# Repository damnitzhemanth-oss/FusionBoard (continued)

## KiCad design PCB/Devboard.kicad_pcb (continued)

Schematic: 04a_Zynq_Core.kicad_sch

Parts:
C121, C122, C123, C124, C125, C126, C127, C128, C129, C130, C131, C132, C133, C134, C135, C136, C137, C138, C139, C140, C141, C142, C143, C144, C145, C146, C147, C148, C149, C150, C151, C152, C153, C155, C156, C157, C158, C159, C160, C161, C162, C163, C164, C165, C166, C167, C168, C169, C170, C171, C172, C173, C175, C176, C177, C178, C179, C180, C181, C182, C183, C184, C185, C186, C187, C188, C189, C190, C191, C192, C193, C194, C195, C196, C197, C198, C199, C200, C201, C202, C203, C204, C205, C206, C207, C208, C209, C210, C211, C212, C213, C214, C215, C216, C217, C218, C219, C220, C221, C222, C223, C224, C225, C226, C227, C228, C229, C230, C231, C232, C233, C234, C235, C236, C237, C238, C239, C240, C241, C242, C243, C244, C245, C246, C247, C248, C249, C250, C251: 0.1uF; C_0402_1005Metric
C154, C174: 47uF; C_1210_3225Metric
R103: 220Ω; R_0402_1005Metric
U27: xczu4evfbvb900pkg; XCZU4EVFBVB900PKG

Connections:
+0V9_GTR: C204.2, C206.2, C217.1, C219.1, U27.A10 (MGTAVCC_R), U27.C10 (MGTAVCC_R), U27.F8 (MGTAVCC_R), U27.H8 (MGTAVCC_R), U27.M8 (MGTAVCC_R), U27.P8 (MGTAVCC_R); also elsewhere on the board
+0V9_VCU: C166.2, C167.2, C183.1, C184.1, U27.AB18 (VCCINT_VCU), U27.AB19 (VCCINT_VCU), U27.AB20 (VCCINT_VCU), U27.AB21 (VCCINT_VCU), U27.V8 (VCCINT_IO); also elsewhere on the board
+0V85: C121.2, C135.2, C136.2, C137.2, C138.2, C139.2, C140.1, C154.1, C155.1, C156.1, C157.1, C158.1, U27.L11 (VCCINT), U27.L13 (VCCINT), U27.L17 (VCCINT), U27.M12 (VCCINT), U27.M14 (VCCINT), U27.M16 (VCCINT), U27.M18 (VCCINT), U27.N11 (VCCINT), U27.N13 (VCCINT), U27.N15 (VCCINT), U27.N17 (VCCINT), U27.P12 (VCCINT), U27.P14 (VCCINT), U27.P16 (VCCINT), U27.R10 (VCCBRAM), U27.R11 (VCCINT), U27.R13 (VCCINT), U27.R17 (VCCINT), U27.T9 (VCCINT_IO), U27.T10 (VCCBRAM), U27.T12 (VCCINT), U27.T16 (VCCINT), U27.U8 (VCCINT_IO), U27.U9 (VCCINT_IO), U27.U10 (VCCBRAM), U27.U11 (VCCINT), U27.U13 (VCCINT), U27.U17 (VCCINT), U27.V10 (VCCBRAM), U27.V12 (VCCINT), U27.V16 (VCCINT), U27.W11 (VCCINT), U27.W13 (VCCINT), U27.W15 (VCCINT), U27.Y12 (VCCINT), U27.Y14 (VCCINT); also elsewhere on the board
+0V85_GTR: C192.2, C201.1, U27.J23 (PS_MGTRAVCC), U27.L23 (PS_MGTRAVCC); also elsewhere on the board
+0V85_PS: C159.2, C161.2, C162.2, C164.2, C165.2, C172.2, C173.2, C174.1, C176.1, C178.1, C179.1, C181.1, C182.1, U27.AA18 (VCC_PSINTFP), U27.AA20 (VCC_PSINTFP), U27.AA21 (VCC_PSINTFP_DDR), U27.AA22 (VCC_PSINTFP_DDR), U27.V17 (VCC_PSINTLP), U27.V18 (VCC_PSINTLP), U27.V19 (VCC_PSINTLP), U27.W17 (VCC_PSINTLP), U27.W19 (VCC_PSINTLP), U27.W20 (VCC_PSINTLP), U27.Y16 (VCC_PSINTFP), U27.Y17 (VCC_PSINTFP), U27.Y18 (VCC_PSINTFP), U27.Y19 (VCC_PSINTFP), U27.Y20 (VCC_PSINTFP), U27.Y22 (VCC_PSINTFP_DDR); also elsewhere on the board
+1V2: C189.2, C191.2, C195.2, C198.1, C200.1, U27.AA4 (VCCO_66), U27.AA24 (VCCO_PSDDR_504), U27.AB27 (VCCO_PSDDR_504), U27.AC25 (VCCO_PSDDR_504), U27.AD3 (VCCO_66), U27.AD8 (VCCO_66), U27.AD28 (VCCO_PSDDR_504), U27.AE26 (VCCO_PSDDR_504), U27.AG27 (VCCO_PSDDR_504), U27.AK26 (VCCO_PSDDR_504); also elsewhere on the board
+1V2_GTH: C207.2, C211.2, C214.2, C215.1, C220.1, C224.1, U27.A6 (MGTAVTT_R), U27.B8 (MGTAVTT_R), U27.C6 (MGTAVTT_R), U27.D8 (MGTAVTT_R), U27.E6 (MGTAVTT_R), U27.G6 (MGTAVTT_R), U27.J6 (MGTAVTT_R), U27.L6 (MGTAVTT_R), U27.N6 (MGTAVTT_R), U27.R6 (MGTAVTT_R), U27.U6 (MGTAVTT_R); also elsewhere on the board
+1V2_PS: C194.2, C203.1, U27.U18 (VCC_PSDDR_PLL), U27.U19 (VCC_PSDDR_PLL); also elsewhere on the board
+1V8: C168.2, C169.2, C170.2, C171.2, C175.2, C185.1, C186.1, C187.1, C188.1, C212.2, C225.1, C229.2, C230.2, C231.2, C232.2, C238.2, C239.1, C243.1, C244.1, C245.1, C246.1, U27.AC15 (VCCO_64), U27.AE11 (VCCO_65), U27.AF14 (VCCO_64), U27.AG7 (VCCO_65), U27.AG17 (VCCO_64), U27.AH10 (VCCO_65), U27.E10 (MGTVCCAUX_R), U27.G10 (MGTVCCAUX_R), U27.K10 (VCCAUX), U27.L10 (VCCAUX), U27.M10 (VCCAUX_IO), U27.N10 (VCCAUX_IO), U27.P10 (VCCAUX_IO), U27.R15 (VCCADC), U27.T22 (VCC_PSAUX), U27.U21 (VCC_PSAUX), U27.V21 (VCC_PSAUX), U27.V22 (VCC_PSAUX); also elsewhere on the board
+1V8_CLEAN: C193.2, C196.2, C202.1, U27.T18 (VCC_PSPLL), U27.T20 (VCC_PSPLL), U27.T21 (VCC_PSPLL); also elsewhere on the board
+1V8_MGTRAVTT: C213.2, C216.2, C226.1, U27.H25 (PS_MGTRAVTT), U27.K25 (PS_MGTRAVTT), U27.L27 (PS_MGTRAVTT); also elsewhere on the board
+1V8_VCCADC: C197.2, U27.W22 (VCC_PSADC); also elsewhere on the board
+3V3: C227.2, C228.2, C233.2, C237.2, C240.2, C241.1, C242.1, C247.1, C251.1, U27.B22 (VCCO_PSIO1_501), U27.B27 (VCCO_PSIO2_502), U27.D13 (VCCO_46), U27.D18 (VCCO_PSIO0_500), U27.D23 (VCCO_PSIO1_501), U27.D28 (VCCO_PSIO2_502), U27.E16 (VCCO_45), U27.E21 (VCCO_PSIO1_501), U27.E26 (VCCO_PSIO2_502), U27.F19 (VCCO_PSIO0_500), U27.G12 (VCCO_46), U27.H15 (VCCO_45), U27.J18 (VCCO_PSIO0_500), U27.N20 (VCCO_PSIO3_503), U27.P18 (VCCO_PSIO3_503); also elsewhere on the board
ADC_CLKOUTM: U27.AE9 (IO_L10P_T1U_N6_QBC_AD4P_65); also elsewhere on the board
ADC_CLKOUTP: U27.AE8 (IO_L10N_T1U_N7_QBC_AD4N_65); also elsewhere on the board
ADC_DA0_M: U27.AK10 (IO_L5N_T0U_N9_AD14N_65); also elsewhere on the board
ADC_DA0_P: U27.AJ10 (IO_L5P_T0U_N8_AD14P_65); also elsewhere on the board
ADC_DA2_M: U27.AJ9 (IO_L8N_T1L_N3_AD5N_65); also elsewhere on the board
ADC_DA2_P: U27.AH9 (IO_L8P_T1L_N2_AD5P_65); also elsewhere on the board
ADC_DA4_M: U27.AK11 (IO_L4N_T0U_N7_DBC_AD7N_65); also elsewhere on the board
ADC_DA4_P: U27.AJ11 (IO_L4P_T0U_N6_DBC_AD7P_SMBALERT_65); also elsewhere on the board
ADC_DA6_M: U27.AJ7 (IO_L12N_T1U_N11_GC_65); also elsewhere on the board
ADC_DA6_P: U27.AJ6 (IO_L13N_T2L_N1_GC_QBC_65); also elsewhere on the board
ADC_DA8_M: U27.AH7 (IO_L12P_T1U_N10_GC_65); also elsewhere on the board
ADC_DA8_P: U27.AH8 (IO_L11N_T1U_N9_GC_65); also elsewhere on the board
ADC_DA10_M: U27.AG10 (IO_L6N_T0U_N11_AD6N_65); also elsewhere on the board
ADC_DA10_P: U27.AF10 (IO_L6P_T0U_N10_AD6P_65); also elsewhere on the board
ADC_DA12_M: U27.AF7 (IO_L9N_T1L_N5_AD12N_65); also elsewhere on the board
ADC_DA12_P: U27.AF8 (IO_L9P_T1L_N4_AD12P_65); also elsewhere on the board
ADC_DB0_M: U27.AK7 (IO_L15P_T2L_N4_AD11P_65); also elsewhere on the board
ADC_DB0_P: U27.AK6 (IO_L15N_T2L_N5_AD11N_65); also elsewhere on the board
ADC_DB2_M: U27.AJ4 (IO_L17P_T2U_N8_AD10P_65); also elsewhere on the board
ADC_DB2_P: U27.AK4 (IO_L17N_T2U_N9_AD10N_65); also elsewhere on the board
ADC_DB4_M: U27.AF5 (IO_L18N_T2U_N11_AD2N_65); also elsewhere on the board
ADC_DB4_P: U27.AF6 (IO_L18P_T2U_N10_AD2P_65); also elsewhere on the board
ADC_DB6_M: U27.AJ1 (IO_L20N_T3L_N3_AD1N_65); also elsewhere on the board
ADC_DB6_P: U27.AJ2 (IO_L20P_T3L_N2_AD1P_65); also elsewhere on the board
ADC_DB8_M: U27.AK2 (IO_L19N_T3L_N1_DBC_AD9N_65); also elsewhere on the board
ADC_DB8_P: U27.AK3 (IO_L19P_T3L_N0_DBC_AD9P_65); also elsewhere on the board
ADC_DB10_M: U27.AG3 (IO_L22N_T3U_N7_DBC_AD0N_65); also elsewhere on the board
ADC_DB10_P: U27.AG4 (IO_L22P_T3U_N6_DBC_AD0P_65); also elsewhere on the board
ADC_DB12_M: U27.AH2 (IO_L21N_T3L_N5_AD8N_65); also elsewhere on the board
ADC_DB12_P: U27.AH3 (IO_L21P_T3L_N4_AD8P_65); also elsewhere on the board
ADS_CS: U27.G16 (IO_L5P_HDGC_45); also elsewhere on the board
ADS_DIN: U27.E17 (IO_L7P_HDGC_45); also elsewhere on the board
ADS_DOUT: U27.E15 (IO_L8P_HDGC_45); also elsewhere on the board
ADS_DRDY: U27.D16 (IO_L9P_AD11P_45); also elsewhere on the board
ADS_SCLK: U27.F16 (IO_L6P_HDGC_45); also elsewhere on the board
ADS_SYNC: U27.C17 (IO_L10P_AD10P_45); also elsewhere on the board
CAM_PWDN: U27.F18 (PS_MIO10); also elsewhere on the board
CAM_RST_N: U27.H18 (PS_MIO12); also elsewhere on the board
DP_AUX_N: U27.E20 (PS_MIO8); also elsewhere on the board
DP_AUX_P: U27.E19 (PS_MIO7); also elsewhere on the board
DP_RX0_N: U27.H28 (PS_MGTRRXN2_505)
DP_RX0_P: U27.H27 (PS_MGTRRXP2_505)
DP_TX0_N: U27.J26 (PS_MGTRTXN2_505); also elsewhere on the board
DP_TX0_P: U27.J25 (PS_MGTRTXP2_505); also elsewhere on the board
EXP_LANE0_RX_N: U27.C3 (MGTHRXN1_226)
EXP_LANE0_RX_P: U27.C4 (MGTHRXP1_226)
EXP_LANE0_TX_N: U27.C7 (MGTHTXN1_226)
EXP_LANE0_TX_P: U27.C8 (MGTHTXP1_226)
EXP_LANE1_RX_N: U27.B1 (MGTHRXN2_226)
EXP_LANE1_RX_P: U27.B2 (MGTHRXP2_226)
EXP_LANE1_TX_N: U27.B5 (MGTHTXN2_226)
EXP_LANE1_TX_P: U27.B6 (MGTHTXP2_226)
EXP_LANE2_RX_N: U27.A3 (MGTHRXN3_226)
EXP_LANE2_RX_P: U27.A4 (MGTHRXP3_226)
EXP_LANE2_TX_N: U27.A7 (MGTHTXN3_226)
EXP_LANE2_TX_P: U27.A8 (MGTHTXP3_226)
EXP_LANE3_RX_N: U27.H1 (MGTHRXN0_225)
EXP_LANE3_RX_P: U27.H2 (MGTHRXP0_225)
EXP_LANE3_TX_N: U27.H5 (MGTHTXN0_225)
EXP_LANE3_TX_P: U27.H6 (MGTHTXP0_225)
EXP_LANE4_RX_N: U27.G3 (MGTHRXN1_225)
EXP_LANE4_RX_P: U27.G4 (MGTHRXP1_225)
EXP_LANE4_TX_N: U27.G7 (MGTHTXN1_225)
EXP_LANE4_TX_P: U27.G8 (MGTHTXP1_225)
FAN_TACH: U27.J21 (PS_MIO48); also elsewhere on the board
GEM_RST: U27.C23 (PS_MIO38); also elsewhere on the board
GEM_RXC: U27.D26 (PS_MIO70); also elsewhere on the board
GEM_RXD0: U27.D30 (PS_MIO71); also elsewhere on the board
GEM_RXD1: U27.E27 (PS_MIO72); also elsewhere on the board
GEM_RXD2: U27.E30 (PS_MIO73); also elsewhere on the board
GEM_RXD3: U27.E29 (PS_MIO74); also elsewhere on the board
GEM_RX_CTL: U27.D29 (PS_MIO75); also elsewhere on the board
GEM_TXC: U27.B30 (PS_MIO64); also elsewhere on the board
GEM_TXD0: U27.D25 (PS_MIO65); also elsewhere on the board
GEM_TXD1: U27.C27 (PS_MIO66); also elsewhere on the board
GEM_TXD2: U27.C28 (PS_MIO67); also elsewhere on the board
GEM_TXD3: U27.C29 (PS_MIO68); also elsewhere on the board
GEM_TX_CTL: U27.D27 (PS_MIO69); also elsewhere on the board
GND: C121.1, C122.1, C123.1, C124.1, C125.1, C126.1, C127.1, C128.1, C129.1, C130.1, C131.1, C132.1, C133.1, C134.1, C135.1, C136.1, C137.1, C138.1, C139.1, C140.2, C141.2, C142.2, C143.2, C144.2, C145.2, C146.2, C147.2, C148.2, C149.2, C150.2, C151.2, C152.2, C153.2, C154.2, C155.2, C156.2, C157.2, C158.2, C159.1, C160.1, C161.1, C162.1, C163.1, C164.1, C165.1, C166.1, C167.1, C168.1, C169.1, C170.1, C171.1, C172.1, C173.1, C174.2, C175.1, C176.2, C177.2, C178.2, C179.2, C180.2, C181.2, C182.2, C183.2, C184.2, C185.2, C186.2, C187.2, C188.2, C189.1, C190.1, C191.1, C193.1, C194.1, C195.1, C196.1, C197.1, C198.2, C199.2, C200.2, C202.2, C203.2, C204.1, C205.1, C206.1, C207.1, C208.1, C209.1, C210.1, C211.1, C212.1, C213.1, C214.1, C215.2, C216.1, C217.2, C218.2, C219.2, C220.2, C221.2, C222.2, C223.2, C224.2, C225.2, C226.2, C227.1, C228.1, C229.1, C230.1, C231.1, C232.1, C233.1, C234.1, C235.1, C236.1, C237.1, C238.1, C239.2, C240.1, C241.2, C242.2, C243.2, C244.2, C245.2, C246.2, C247.2, C248.2, C249.2, C250.2, C251.2, R103.2, U27.A1 (GND), U27.A2 (GND), U27.A5 (GND), U27.A9 (GND), U27.A11 (GND), U27.A30 (GND), U27.AA9 (GND), U27.AA19 (GND), U27.AA29 (GND), U27.AB2 (GND), U27.AB7 (GND), U27.AB12 (GND), U27.AB17 (GND), U27.AB22 (GND), U27.AC5 (GND), U27.AC10 (GND), U27.AC20 (GND), U27.AD13 (GND), U27.AD18 (GND), U27.AD23 (GND), U27.AE6 (GND), U27.AE16 (GND), U27.AE21 (GND), U27.AF4 (GND), U27.AF9 (GND), U27.AF19 (GND), U27.AF24 (GND), U27.AF29 (GND), U27.AG2 (GND), U27.AG12 (GND), U27.AG22 (GND), U27.AH5 (GND), U27.AH15 (GND), U27.AH20 (GND), U27.AH25 (GND), U27.AJ3 (GND), U27.AJ8 (GND), U27.AJ13 (GND), U27.AJ18 (GND), U27.AJ23 (GND), U27.AJ28 (GND), U27.AK1 (GND), U27.AK30 (GND), U27.B3 (GND), U27.B4 (GND), U27.B7 (GND), U27.B11 (GND), U27.B13 (GND), U27.B17 (GND), U27.C1 (GND), U27.C2 (GND), U27.C5 (GND), U27.C9 (GND), U27.C11 (GND), U27.C15 (GND), U27.C20 (GND), U27.C25 (GND), U27.C30 (GND), U27.D3 (GND), U27.D4 (GND), U27.D7 (GND), U27.D11 (GND), U27.E1 (GND), U27.E2 (GND), U27.E5 (GND), U27.E9 (GND), U27.E11 (GND), U27.F3 (GND), U27.F4 (GND), U27.F7 (GND), U27.F11 (GND), U27.F14 (GND), U27.F24 (GND), U27.F25 (GND), U27.F26 (GND), U27.F27 (GND), U27.F28 (GND), U27.F29 (GND), U27.F30 (GND), U27.G1 (GND), U27.G2 (GND), U27.G5 (GND), U27.G9 (GND), U27.G11 (GND), U27.G17 (GND), U27.G22 (GND), U27.G23 (GND), U27.G24 (GND), U27.G27 (GND), U27.G28 (GND), U27.H3 (GND), U27.H4 (GND), U27.H7 (GND), U27.H11 (GND), U27.H20 (GND), U27.H22 (GND), U27.H26 (GND), U27.H29 (GND), U27.H30 (GND), U27.J1 (GND), U27.J2 (GND), U27.J5 (GND), U27.J9 (GND), U27.J10 (GND), U27.J11 (GND), U27.J13 (GND), U27.J22 (GND), U27.J24 (GND), U27.J27 (GND), U27.J28 (GND), U27.K3 (GND), U27.K4 (GND), U27.K9 (GND), U27.K22 (GND), U27.K26 (GND), U27.K29 (GND), U27.K30 (GND), U27.L1 (GND), U27.L2 (GND), U27.L5 (GND), U27.L9 (GND), U27.L12 (GND), U27.L16 (GND), U27.L18 (GND), U27.L22 (GND), U27.L24 (GND), U27.L28 (GND), U27.M3 (GND), U27.M4 (GND), U27.M7 (GND), U27.M9 (GND), U27.M11 (GND), U27.M13 (GND), U27.M15 (GND), U27.M17 (GND), U27.M22 (GND), U27.M26 (GND), U27.M29 (GND), U27.M30 (GND), U27.N1 (GND), U27.N2 (GND), U27.N5 (GND), U27.N9 (GND), U27.N12 (GND), U27.N14 (GND), U27.N16 (GND), U27.N23 (GND), U27.N24 (GND), U27.N25 (GND), U27.N26 (GND), U27.N27 (GND), U27.N28 (GND), U27.N29 (GND), U27.N30 (GND), U27.P3 (GND), U27.P4 (GND), U27.P7 (GND), U27.P9 (GND), U27.P11 (GND), U27.P13 (GND), U27.P15 (GND), U27.P17 (GND), U27.R1 (GND), U27.R2 (GND), U27.R5 (GND), U27.R9 (GND), U27.R12 (GND), U27.R14 (GNDADC), U27.R16 (GND), U27.R21 (GND), U27.R26 (GND), U27.T3 (GND), U27.T4 (GND), U27.T7 (GND), U27.T8 (GND), U27.T11 (GND), U27.T13 (GND), U27.T14 (VREFN), U27.T17 (GND), U27.T19 (GND), U27.T24 (GND), U27.T29 (GND), U27.U1 (GND), U27.U2 (GND), U27.U5 (GND), U27.U7 (GND), U27.U12 (GND), U27.U16 (GND), U27.U20 (VCC_PSBATT), U27.U22 (GND), U27.U27 (GND), U27.V3 (GND), U27.V4 (GND), U27.V7 (GND), U27.V9 (GND), U27.V11 (GND), U27.V13 (GND), U27.V20 (GND), U27.V25 (GND), U27.W1 (GND), U27.W2 (GND), U27.W5 (GND), U27.W6 (GND), U27.W12 (GND), U27.W14 (GND), U27.W16 (GND), U27.W18 (GND), U27.W21 (GND_PSADC), U27.W23 (GND), U27.W28 (GND), U27.Y2 (GND), U27.Y3 (GND), U27.Y4 (GND), U27.Y5 (GND), U27.Y11 (GND), U27.Y13 (GND), U27.Y15 (GND), U27.Y21 (GND), U27.Y26 (GND); also elsewhere on the board
GNSS_PPS: U27.F20 (PS_MIO9); also elsewhere on the board
GPIO_BMC_IRQ: U27.B24 (PS_MIO34)
GPIO_BOOT_LED: U27.F21 (PS_MIO37)
GPIO_ESP_IRQ: U27.K21 (PS_MIO47)
GPIO_EXP_RST: U27.K20 (PS_MIO46)
GPIO_PD_IRQ: U27.B23 (PS_MIO35), U27.G18 (PS_MIO11)
GPIO_SD1_PWR_EN: U27.D22 (PS_MIO36)
GTH_REFCLK0_156M_N: U27.D9 (MGTREFCLK0N_226)
GTH_REFCLK0_156M_P: U27.D10 (MGTREFCLK0P_226)
GTH_REFCLK1_156M_N: U27.B9 (MGTREFCLK1N_226)
GTH_REFCLK1_156M_P: U27.B10 (MGTREFCLK1P_226)
I2C0_SCL: U27.A22 (PS_MIO31); also elsewhere on the board
I2C0_SDA: U27.C22 (PS_MIO33); also elsewhere on the board
I2C1_SCL: U27.C21 (PS_MIO30); also elsewhere on the board
I2C1_SDA: U27.G20 (PS_MIO32); also elsewhere on the board
LMS_SCK: U27.J16 (IO_L4P_AD12P_45); also elsewhere on the board
LMX_CSB: U27.J15 (IO_L3P_AD13P_45); also elsewhere on the board
LMX_MUXOUT: U27.L15 (IO_L1P_AD15P_45); also elsewhere on the board
LMX_SDI: U27.K15 (IO_L2P_AD14P_45); also elsewhere on the board
MDIO_MDC: U27.E28 (PS_MIO76); also elsewhere on the board
MDIO_MDIO: U27.E25 (PS_MIO77); also elsewhere on the board
MIO50: U27.J20 (PS_MIO50); also elsewhere on the board
MIO51: U27.H21 (PS_MIO51); also elsewhere on the board
MIPI_CLK_N: U27.AC11 (IO_L3N_T0L_N5_AD15N_66); also elsewhere on the board
MIPI_CLK_P: U27.AB11 (IO_L3P_T0L_N4_AD15P_66); also elsewhere on the board
MIPI_D0_N: U27.AA11 (IO_L2N_T0L_N3_66); also elsewhere on the board
MIPI_D0_P: U27.AA12 (IO_L2P_T0L_N2_66); also elsewhere on the board
MIPI_D1_N: U27.AD12 (IO_L1N_T0L_N1_DBC_66); also elsewhere on the board
MIPI_D1_P: U27.AC12 (IO_L1P_T0L_N0_DBC_66); also elsewhere on the board
MIPI_D2_N: U27.AD10 (IO_L4N_T0U_N7_DBC_AD7N_66); also elsewhere on the board
MIPI_D2_P: U27.AD11 (IO_L4P_T0U_N6_DBC_AD7P_66); also elsewhere on the board
MIPI_D3_N: U27.AB9 (IO_L5N_T0U_N9_AD14N_66); also elsewhere on the board
MIPI_D3_P: U27.AB10 (IO_L5P_T0U_N8_AD14P_66); also elsewhere on the board
unnamed: C122.2, C141.1
unnamed: C123.2, C142.1
unnamed: C124.2, C143.1
unnamed: C125.2, C144.1
unnamed: C126.2, C145.1
unnamed: C127.2, C146.1
unnamed: C128.2, C147.1
unnamed: C129.2, C148.1
unnamed: C130.2, C149.1
unnamed: C131.2, C150.1
unnamed: C132.2, C151.1
unnamed: C133.2, C152.1
unnamed: C134.2, C153.1
unnamed: C160.2, C177.1
unnamed: C163.2, C180.1
unnamed: C190.2, C199.1
unnamed: C192.1, C201.2
unnamed: C205.2, C218.1
unnamed: C208.2, C221.1
unnamed: C209.2, C222.1
unnamed: C210.2, C223.1
unnamed: C234.2, C248.1
unnamed: C235.2, C249.1
unnamed: C236.2, C250.1
unnamed: R103.1, U27.M25 (PS_MGTRREF_505)
PCIE_RX_N: U27.J30 (PS_MGTRRXN1_505); also elsewhere on the board
PCIE_RX_P: U27.J29 (PS_MGTRRXP1_505); also elsewhere on the board
PCIE_TX_N: U27.K28 (PS_MGTRTXN1_505); also elsewhere on the board
PCIE_TX_P: U27.K27 (PS_MGTRTXP1_505); also elsewhere on the board
PS_DDR_A0: U27.AH30 (PS_DDR_A0); also elsewhere on the board
PS_DDR_A1: U27.AG30 (PS_DDR_A1); also elsewhere on the board
PS_DDR_A2: U27.AK29 (PS_DDR_A2); also elsewhere on the board
PS_DDR_A3: U27.AJ30 (PS_DDR_A3); also elsewhere on the board
PS_DDR_A4: U27.AK28 (PS_DDR_A4); also elsewhere on the board
PS_DDR_A5: U27.AK27 (PS_DDR_A5); also elsewhere on the board
PS_DDR_A6: U27.AF27 (PS_DDR_A6); also elsewhere on the board
PS_DDR_A7: U27.AE27 (PS_DDR_A7); also elsewhere on the board
PS_DDR_A8: U27.AF26 (PS_DDR_A8); also elsewhere on the board
PS_DDR_A9: U27.AG26 (PS_DDR_A9); also elsewhere on the board
PS_DDR_A10: U27.AE29 (PS_DDR_A10); also elsewhere on the board
PS_DDR_A11: U27.AE28 (PS_DDR_A11); also elsewhere on the board
PS_DDR_A12: U27.AH29 (PS_DDR_A12); also elsewhere on the board
PS_DDR_A13: U27.AH28 (PS_DDR_A13); also elsewhere on the board
PS_DDR_A14: U27.AG29 (PS_DDR_A14); also elsewhere on the board
PS_DDR_A15: U27.AJ29 (PS_DDR_A15); also elsewhere on the board
PS_DDR_A16: U27.AH27 (PS_DDR_A16); also elsewhere on the board
PS_DDR_A17: U27.AJ27 (PS_DDR_A17)
PS_DDR_ACT_N: U27.AD26 (PS_DDR_ACT_N); also elsewhere on the board
PS_DDR_ALERT_N: U27.AB24 (PS_DDR_ALERT_N); also elsewhere on the board
PS_DDR_BA0: U27.AD27 (PS_DDR_BA0); also elsewhere on the board
PS_DDR_BA1: U27.AC26 (PS_DDR_BA1); also elsewhere on the board
PS_DDR_BG0: U27.AC28 (PS_DDR_BG0); also elsewhere on the board
PS_DDR_BG1: U27.AC27 (PS_DDR_BG1)
PS_DDR_CK0: U27.AE30 (PS_DDR_CK0); also elsewhere on the board
PS_DDR_CK1: U27.AF28 (PS_DDR_CK1)
PS_DDR_CKE0: U27.AC30 (PS_DDR_CKE0); also elsewhere on the board
PS_DDR_CKE1: U27.AB28 (PS_DDR_CKE1)
PS_DDR_CK_N0: U27.AF30 (PS_DDR_CK_N0); also elsewhere on the board
PS_DDR_CK_N1: U27.AG28 (PS_DDR_CK_N1)
PS_DDR_CS_N0: U27.AD30 (PS_DDR_CS_N0); also elsewhere on the board
PS_DDR_CS_N1: U27.AD29 (PS_DDR_CS_N1)
PS_DDR_DM0: U27.AJ20 (PS_DDR_DM0); also elsewhere on the board
PS_DDR_DM1: U27.AJ25 (PS_DDR_DM1); also elsewhere on the board
PS_DDR_DM2: U27.AF21 (PS_DDR_DM2); also elsewhere on the board
PS_DDR_DM3: U27.AE25 (PS_DDR_DM3); also elsewhere on the board
PS_DDR_DM4: U27.Y24 (PS_DDR_DM4); also elsewhere on the board
PS_DDR_DM5: U27.R24 (PS_DDR_DM5); also elsewhere on the board
PS_DDR_DM6: U27.V28 (PS_DDR_DM6); also elsewhere on the board
PS_DDR_DM7: U27.P28 (PS_DDR_DM7); also elsewhere on the board
PS_DDR_DM8: U27.AA27 (PS_DDR_DM8)
PS_DDR_DQ0: U27.AH22 (PS_DDR_DQ0); also elsewhere on the board
PS_DDR_DQ1: U27.AH21 (PS_DDR_DQ1); also elsewhere on the board
PS_DDR_DQ2: U27.AJ22 (PS_DDR_DQ2); also elsewhere on the board
PS_DDR_DQ3: U27.AK22 (PS_DDR_DQ3); also elsewhere on the board
PS_DDR_DQ4: U27.AK20 (PS_DDR_DQ4); also elsewhere on the board
PS_DDR_DQ5: U27.AJ19 (PS_DDR_DQ5); also elsewhere on the board
PS_DDR_DQ6: U27.AK19 (PS_DDR_DQ6); also elsewhere on the board
PS_DDR_DQ7: U27.AH19 (PS_DDR_DQ7); also elsewhere on the board
PS_DDR_DQ8: U27.AH23 (PS_DDR_DQ8); also elsewhere on the board
PS_DDR_DQ9: U27.AK23 (PS_DDR_DQ9); also elsewhere on the board
PS_DDR_DQ10: U27.AG24 (PS_DDR_DQ10); also elsewhere on the board
PS_DDR_DQ11: U27.AK24 (PS_DDR_DQ11); also elsewhere on the board
PS_DDR_DQ12: U27.AJ26 (PS_DDR_DQ12); also elsewhere on the board
PS_DDR_DQ13: U27.AK25 (PS_DDR_DQ13); also elsewhere on the board
PS_DDR_DQ14: U27.AG25 (PS_DDR_DQ14); also elsewhere on the board
PS_DDR_DQ15: U27.AH26 (PS_DDR_DQ15); also elsewhere on the board
PS_DDR_DQ16: U27.AD22 (PS_DDR_DQ16); also elsewhere on the board
PS_DDR_DQ17: U27.AE22 (PS_DDR_DQ17); also elsewhere on the board
PS_DDR_DQ18: U27.AF22 (PS_DDR_DQ18); also elsewhere on the board
PS_DDR_DQ19: U27.AG21 (PS_DDR_DQ19); also elsewhere on the board
PS_DDR_DQ20: U27.AD20 (PS_DDR_DQ20); also elsewhere on the board
PS_DDR_DQ21: U27.AF20 (PS_DDR_DQ21); also elsewhere on the board
PS_DDR_DQ22: U27.AE20 (PS_DDR_DQ22); also elsewhere on the board
PS_DDR_DQ23: U27.AG20 (PS_DDR_DQ23); also elsewhere on the board
PS_DDR_DQ24: U27.AG23 (PS_DDR_DQ24); also elsewhere on the board
PS_DDR_DQ25: U27.AF23 (PS_DDR_DQ25); also elsewhere on the board
PS_DDR_DQ26: U27.AF25 (PS_DDR_DQ26); also elsewhere on the board
PS_DDR_DQ27: U27.AE23 (PS_DDR_DQ27); also elsewhere on the board
PS_DDR_DQ28: U27.AC22 (PS_DDR_DQ28); also elsewhere on the board
PS_DDR_DQ29: U27.AC23 (PS_DDR_DQ29); also elsewhere on the board
PS_DDR_DQ30: U27.AD25 (PS_DDR_DQ30); also elsewhere on the board
PS_DDR_DQ31: U27.AC24 (PS_DDR_DQ31); also elsewhere on the board
PS_DDR_DQ32: U27.U24 (PS_DDR_DQ32); also elsewhere on the board
PS_DDR_DQ33: U27.V23 (PS_DDR_DQ33); also elsewhere on the board
PS_DDR_DQ34: U27.U25 (PS_DDR_DQ34); also elsewhere on the board
PS_DDR_DQ35: U27.V24 (PS_DDR_DQ35); also elsewhere on the board
PS_DDR_DQ36: U27.Y25 (PS_DDR_DQ36); also elsewhere on the board
PS_DDR_DQ37: U27.AA23 (PS_DDR_DQ37); also elsewhere on the board
PS_DDR_DQ38: U27.AA25 (PS_DDR_DQ38); also elsewhere on the board
PS_DDR_DQ39: U27.Y23 (PS_DDR_DQ39); also elsewhere on the board
PS_DDR_DQ40: U27.P23 (PS_DDR_DQ40); also elsewhere on the board
PS_DDR_DQ41: U27.R23 (PS_DDR_DQ41); also elsewhere on the board
PS_DDR_DQ42: U27.T23 (PS_DDR_DQ42); also elsewhere on the board
PS_DDR_DQ43: U27.P26 (PS_DDR_DQ43); also elsewhere on the board
PS_DDR_DQ44: U27.T25 (PS_DDR_DQ44); also elsewhere on the board
PS_DDR_DQ45: U27.U23 (PS_DDR_DQ45); also elsewhere on the board
PS_DDR_DQ46: U27.T26 (PS_DDR_DQ46); also elsewhere on the board
PS_DDR_DQ47: U27.P24 (PS_DDR_DQ47); also elsewhere on the board
PS_DDR_DQ48: U27.U26 (PS_DDR_DQ48); also elsewhere on the board
PS_DDR_DQ49: U27.V26 (PS_DDR_DQ49); also elsewhere on the board
PS_DDR_DQ50: U27.U28 (PS_DDR_DQ50); also elsewhere on the board
PS_DDR_DQ51: U27.V27 (PS_DDR_DQ51); also elsewhere on the board
PS_DDR_DQ52: U27.U30 (PS_DDR_DQ52); also elsewhere on the board
PS_DDR_DQ53: U27.V30 (PS_DDR_DQ53); also elsewhere on the board
PS_DDR_DQ54: U27.W30 (PS_DDR_DQ54); also elsewhere on the board
PS_DDR_DQ55: U27.W29 (PS_DDR_DQ55); also elsewhere on the board
PS_DDR_DQ56: U27.R30 (PS_DDR_DQ56); also elsewhere on the board
PS_DDR_DQ57: U27.T30 (PS_DDR_DQ57); also elsewhere on the board
PS_DDR_DQ58: U27.P30 (PS_DDR_DQ58); also elsewhere on the board
PS_DDR_DQ59: U27.P29 (PS_DDR_DQ59); also elsewhere on the board
PS_DDR_DQ60: U27.T28 (PS_DDR_DQ60); also elsewhere on the board
PS_DDR_DQ61: U27.T27 (PS_DDR_DQ61); also elsewhere on the board
PS_DDR_DQ62: U27.P27 (PS_DDR_DQ62); also elsewhere on the board
PS_DDR_DQ63: U27.R27 (PS_DDR_DQ63); also elsewhere on the board
PS_DDR_DQ64: U27.AB29 (PS_DDR_DQ64)
PS_DDR_DQ65: U27.AA30 (PS_DDR_DQ65)
PS_DDR_DQ66: U27.Y30 (PS_DDR_DQ66)
PS_DDR_DQ67: U27.Y29 (PS_DDR_DQ67)
PS_DDR_DQ68: U27.AA26 (PS_DDR_DQ68)
PS_DDR_DQ69: U27.W27 (PS_DDR_DQ69)
PS_DDR_DQ70: U27.Y27 (PS_DDR_DQ70)
PS_DDR_DQ71: U27.W26 (PS_DDR_DQ71)
PS_DDR_DQS_N0: U27.AK21 (PS_DDR_DQS_N0); also elsewhere on the board
PS_DDR_DQS_N1: U27.AJ24 (PS_DDR_DQS_N1); also elsewhere on the board
PS_DDR_DQS_N2: U27.AD21 (PS_DDR_DQS_N2); also elsewhere on the board
PS_DDR_DQS_N3: U27.AE24 (PS_DDR_DQS_N3); also elsewhere on the board
PS_DDR_DQS_N4: U27.W25 (PS_DDR_DQS_N4); also elsewhere on the board
PS_DDR_DQS_N5: U27.R25 (PS_DDR_DQS_N5); also elsewhere on the board
PS_DDR_DQS_N6: U27.V29 (PS_DDR_DQS_N6); also elsewhere on the board
PS_DDR_DQS_N7: U27.R29 (PS_DDR_DQS_N7); also elsewhere on the board
PS_DDR_DQS_N8: U27.AA28 (PS_DDR_DQS_N8)
PS_DDR_DQS_P0: U27.AJ21 (PS_DDR_DQS_P0); also elsewhere on the board
PS_DDR_DQS_P1: U27.AH24 (PS_DDR_DQS_P1); also elsewhere on the board
PS_DDR_DQS_P2: U27.AC21 (PS_DDR_DQS_P2); also elsewhere on the board
PS_DDR_DQS_P3: U27.AD24 (PS_DDR_DQS_P3); also elsewhere on the board
PS_DDR_DQS_P4: U27.W24 (PS_DDR_DQS_P4); also elsewhere on the board
PS_DDR_DQS_P5: U27.P25 (PS_DDR_DQS_P5); also elsewhere on the board
PS_DDR_DQS_P6: U27.U29 (PS_DDR_DQS_P6); also elsewhere on the board
PS_DDR_DQS_P7: U27.R28 (PS_DDR_DQS_P7); also elsewhere on the board
PS_DDR_DQS_P8: U27.Y28 (PS_DDR_DQS_P8)
PS_DDR_ODT0: U27.AB30 (PS_DDR_ODT0); also elsewhere on the board
PS_DDR_ODT1: U27.AC29 (PS_DDR_ODT1)
PS_DDR_PARITY: U27.AB26 (PS_DDR_PARITY); also elsewhere on the board
PS_DDR_RAM_RST_N: U27.AB25 (PS_DDR_RAM_RST_N); also elsewhere on the board
PS_DONE: U27.N22 (PS_DONE)
PS_ERROR_OUT: U27.R22 (PS_ERROR_OUT)
PS_ERROR_STATUS: U27.R20 (PS_ERROR_STATUS)
PS_INIT_B: U27.N18 (PS_INIT_B)
PS_JTAG_TCK: U27.L19 (PS_JTAG_TCK); also elsewhere on the board
PS_JTAG_TDI: U27.L20 (PS_JTAG_TDI); also elsewhere on the board
PS_JTAG_TDO: U27.M20 (PS_JTAG_TDO); also elsewhere on the board
PS_JTAG_TMS: U27.L21 (PS_JTAG_TMS); also elsewhere on the board
PS_MODE0: U27.R18 (PS_MODE0)
PS_MODE1: U27.R19 (PS_MODE1)
PS_MODE2: U27.P21 (PS_MODE2)
PS_MODE3: U27.P22 (PS_MODE3)
PS_POR_B: U27.N19 (PS_POR_B); also elsewhere on the board
PS_PROG_B: U27.M19 (PS_PROG_B)
PS_REFCLK0_100M_N: U27.M24 (PS_MGTREFCLK0N_505)
PS_REFCLK0_100M_P: U27.M23 (PS_MGTREFCLK0P_505)
PS_REFCLK1_27M_N: U27.L26 (PS_MGTREFCLK1N_505)
PS_REFCLK1_27M_P: U27.L25 (PS_MGTREFCLK1P_505)
PS_REF_CLK: U27.P19 (PS_REF_CLK); also elsewhere on the board
PS_SRST_B: U27.P20 (PS_SRST_B); also elsewhere on the board
QSPI_FEEDBACK_CLK: U27.D20 (PS_MIO6)
QSPI_IO0: U27.A20 (PS_MIO1); also elsewhere on the board
QSPI_IO1: U27.B19 (PS_MIO2); also elsewhere on the board
QSPI_IO2: U27.D19 (PS_MIO3); also elsewhere on the board
QSPI_IO3: U27.J17 (PS_MIO4); also elsewhere on the board
QSPI_SCLK: U27.H17 (PS_MIO0); also elsewhere on the board
QSPI_SS: U27.C19 (PS_MIO5); also elsewhere on the board
SD0_CD: U27.A18 (PS_MIO24)
SD0_CLK: U27.G19 (PS_MIO13); also elsewhere on the board
SD0_CMD: U27.E18 (PS_MIO14); also elsewhere on the board
SD0_D0: U27.J19 (PS_MIO15); also elsewhere on the board
SD0_D1: U27.K17 (PS_MIO16); also elsewhere on the board
SD0_D2: U27.C18 (PS_MIO17); also elsewhere on the board
SD0_D3: U27.K18 (PS_MIO18); also elsewhere on the board
SD0_D4: U27.K16 (PS_MIO19); also elsewhere on the board
SD0_D5: U27.A19 (PS_MIO20); also elsewhere on the board
SD0_D6: U27.H19 (PS_MIO21); also elsewhere on the board
SD0_D7: U27.F17 (PS_MIO22); also elsewhere on the board
SD0_RST: U27.K19 (PS_MIO23); also elsewhere on the board
SD0_WP: U27.B18 (PS_MIO25)
SD1_CD: U27.F23 (PS_MIO45); also elsewhere on the board
SD1_CLK: U27.E22 (PS_MIO39); also elsewhere on the board
SD1_CMD: U27.C24 (PS_MIO40); also elsewhere on the board
SD1_D0: U27.D24 (PS_MIO41); also elsewhere on the board
SD1_D1: U27.E23 (PS_MIO42); also elsewhere on the board
SD1_D2: U27.F22 (PS_MIO43); also elsewhere on the board
SD1_D3: U27.E24 (PS_MIO44); also elsewhere on the board
SFP_RX_N: U27.D1 (MGTHRXN0_226); also elsewhere on the board
SFP_RX_P: U27.D2 (MGTHRXP0_226); also elsewhere on the board
SFP_TX_N: U27.D5 (MGTHTXN0_226); also elsewhere on the board
SFP_TX_P: U27.D6 (MGTHTXP0_226); also elsewhere on the board
SYSMON_DXN: U27.V14 (DXN)
SYSMON_DXP: U27.V15 (DXP)
SYSMON_VN: U27.U14 (VN)
SYSMON_VP: U27.T15 (VP)
SYSMON_VREFP: U27.U15 (VREFP)
UART0_RX: U27.D21 (PS_MIO29); also elsewhere on the board
UART0_TX: U27.B20 (PS_MIO26); also elsewhere on the board
UART1_RX: U27.A21 (PS_MIO28); also elsewhere on the board
UART1_TX: U27.B21 (PS_MIO27); also elsewhere on the board
USB2_CLK: U27.A24 (PS_MIO52); also elsewhere on the board
USB2_D0: U27.A25 (PS_MIO56); also elsewhere on the board
USB2_D1: U27.A26 (PS_MIO57); also elsewhere on the board
USB2_D2: U27.A28 (PS_MIO58); also elsewhere on the board
USB2_D3: U27.A27 (PS_MIO59); also elsewhere on the board
USB2_D4: U27.C26 (PS_MIO60); also elsewhere on the board
USB2_D5: U27.B29 (PS_MIO61); also elsewhere on the board
USB2_D6: U27.B28 (PS_MIO62); also elsewhere on the board
USB2_D7: U27.A29 (PS_MIO63); also elsewhere on the board
USB2_DIR: U27.B25 (PS_MIO53); also elsewhere on the board
USB2_NXT: U27.A23 (PS_MIO54); also elsewhere on the board
USB2_STP: U27.B26 (PS_MIO55); also elsewhere on the board
USB3_RX_N: U27.L30 (PS_MGTRRXN0_505); also elsewhere on the board
USB3_RX_P: U27.L29 (PS_MGTRRXP0_505); also elsewhere on the board
USB3_TX_N: U27.M28 (PS_MGTRTXN0_505); also elsewhere on the board
USB3_TX_P: U27.M27 (PS_MGTRTXP0_505); also elsewhere on the board
USB3_VBUS_NET: U27.G21 (PS_MIO49); also elsewhere on the board

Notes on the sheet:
VCCINT
VCCADC
VCC_45+46
VCC_PSIO
VCCINT_IO
VCCO_PSDDR_504
VCC_PSAUX
VCC_PSPLL
MGTVCCAUX
VREFP
PS_MGTRAVTT
DECOUPLING CAPACITORS
VCCINT_VCU
VCC_PSADC
SECTION 04a : Zynq Core
VCCO_64+65+66
MGTAVCC
VCCAUX+IO
VCCBRAM
VCC_PSDDR_PLL
VCC_PSINTFP + PSINTLP + DDR
PS_MGTRAVCC

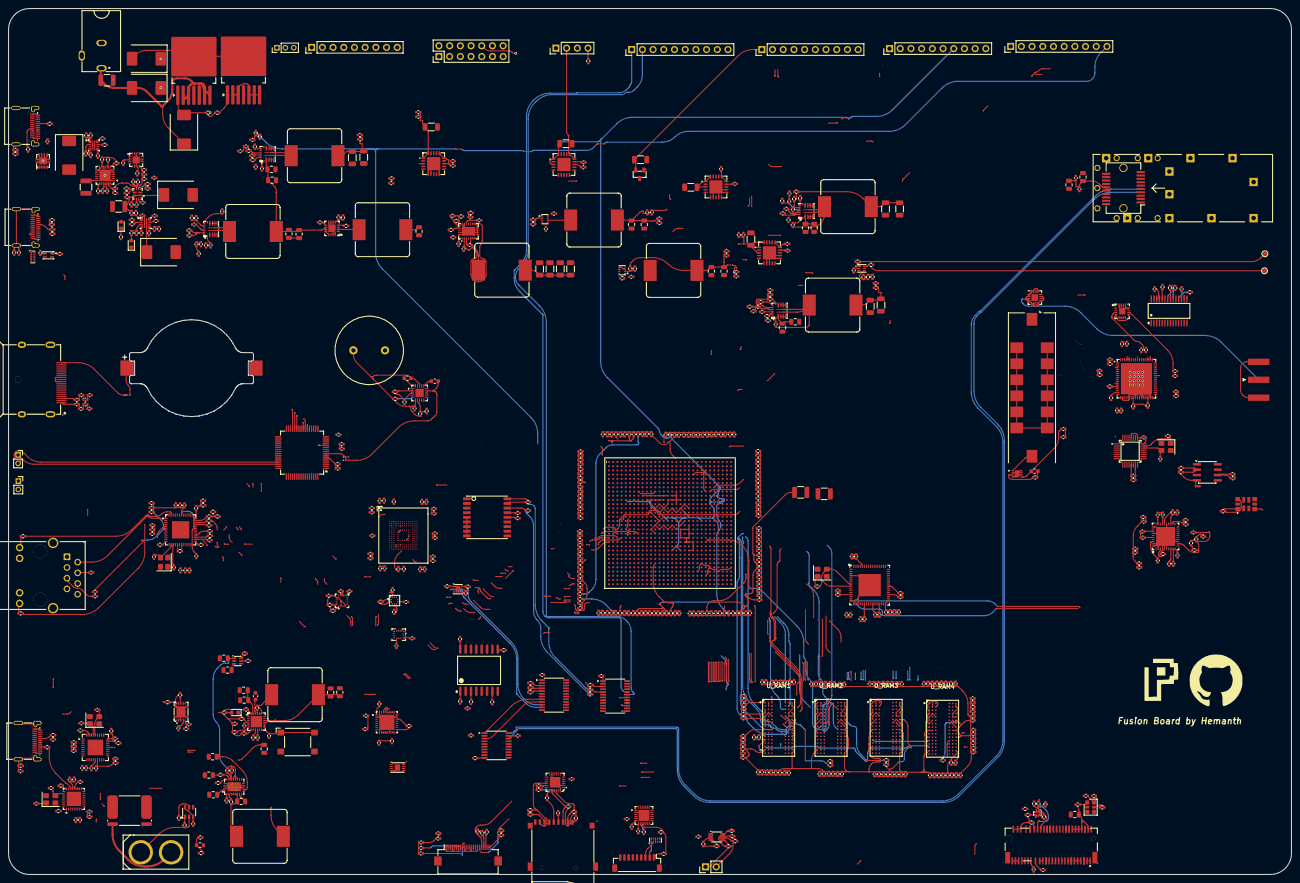
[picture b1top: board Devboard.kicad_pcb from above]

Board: 16 copper layers, 304.6 x 205.6 mm, 875 parts (0 on the bottom side), 644 nets.

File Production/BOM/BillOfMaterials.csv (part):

"Reference","Qty","Value","DNP","Exclude from BOM","Exclude from Board","Exclude from Simulation","Exclude from Position Files","Footprint","Datasheet","Description","#","LCSC Part"
"BT1","1","Battery_Cell","","","","","${EXCLUDE_FROM_POS_FILES}","Battery:BatteryHolder_Keystone_1057_1x2032","","Single-cell battery","1",""
"C1,C3,C8","3","1uF","","","","","${EXCLUDE_FROM_POS_FILES}","Capacitor_SMD:C_1210_3225Metric","","Unpolarized capacitor","2",""
"C2,C9,C15","3","100uF 35V","","","","","${EXCLUDE_FROM_POS_FILES}","Capacitor_SMD:C_1210_3225Metric","","Unpolarized capacitor","3",""
"C4","1","100nF","","","","","${EXCLUDE_FROM_POS_FILES}","Capacitor_SMD:C_1210_3225Metric","","Unpolarized capacitor","4",""
"C5,C10","2","1uF 25V","","","","","${EXCLUDE_FROM_POS_FILES}","Capacitor_SMD:C_0402_1005Metric","","Unpolarized capacitor","5",""
"C6","1","2.2uF","","","","","${EXCLUDE_FROM_POS_FILES}","Capacitor_SMD:C_0402_1005Metric","","Unpolarized capacitor","6",""
"C7,C26,C31,C412,C413,C414,C415,C416,C417,C418,C419,C420,C421,C423,C425,C426,C427,C428,C430,C448,C449,C450,C452,C456,C458,C460,C461,C462,C463,C464,C467,C471,C476,C480,C491,C492,C500","37","100nF","","","","","${EXCLUDE_FROM_POS_FILES}","Capacitor_SMD:C_0402_1005Metric","","Unpolarized capacitor","7",""
"C11","1","0.1uF 50V X7R","","","","","${EXCLUDE_FROM_POS_FILES}","Capacitor_SMD:C_0402_1005Metric","","Unpolarized capacitor","8",""
"C12,C13,C20","3","10nF 25V","","","","","${EXCLUDE_FROM_POS_FILES}","Capacitor_SMD:C_0402_1005Metric","","Unpolarized capacitor","9",""
"C14,C81,C85,C111,C_shield1","5","4.7nF 50V","","","","","${EXCLUDE_FROM_POS_FILES}","Capacitor_SMD:C_0402_1005Metric","","Unpolarized capacitor","10",""
"C16","1","2.2nF 25V","","","","","${EXCLUDE_FROM_POS_FILES}","Capacitor_SMD:C_0402_1005Metric","","Unpolarized capacitor","11",""
"C17,C18,C66,C68,C70,C72,C74,C94,C105,C119","10","0.1uF 25V","","","","","${EXCLUDE_FROM_POS_FILES}","Capacitor_SMD:C_0402_1005Metric","","Unpolarized capacitor","12",""
"C19,C21","2","0.1uF 50V","","","","","${EXCLUDE_FROM_POS_FILES}","Capacitor_SMD:C_0402_1005Metric","","Unpolarized capacitor","13",""
"C22","1","47nF","","","","","${EXCLUDE_FROM_POS_FILES}","Capacitor_SMD:C_0402_1005Metric","","Unpolarized capacitor","14",""
"C23,C24,C28,C29,C30,C50,C52,C60,C61,C64,C65","11","22uF","","","","","${EXCLUDE_FROM_POS_FILES}","Capacitor_SMD:C_0805_2012Metric","","Unpolarized capacitor","15",""
"C25,C45,C48,C62,C101,C102,C117,C342,C344,C346,C348,C350,C352,C353,C355,C357,C359,C361,C391,C393,C394,C395,C396,C398,C400,C404,C457,C459,C466,C468,C470,C472,C479,C497,C498","35","1uF","","","","","${EXCLUDE_FROM_POS_FILES}","Capacitor_SMD:C_0402_1005Metric","","Unpolarized capacitor","16",""
"C27","1","4.7uF","","","","","${EXCLUDE_FROM_POS_FILES}","Capacitor_SMD:C_0603_1608Metric","","Unpolarized capacitor","17",""
"C32,C33,C37","3","1uF","","","","","${EXCLUDE_FROM_POS_FILES}","Capacitor_SMD:C_0805_2012Metric","","Unpolarized capacitor","18",""
"C34","1","0.47uF","","","","","${EXCLUDE_FROM_POS_FILES}","Capacitor_SMD:C_0402_1005Metric","","Unpolarized capacitor","19",""
"C35,C39","2","10nF","","","","","${EXCLUDE_FROM_POS_FILES}","Capacitor_SMD:C_0805_2012Metric","","Unpolarized capacitor","20",""
"C36,C58,C59,C63,C67,C69,C71,C73,C75,C95,C98,C100,C106,C108,C120,C451,C453,C454,C455,C465,C469,C484,C486,C488,C490,C507","26","10uF","","","","","${EXCLUDE_FROM_POS_FILES}","Capacitor_SMD:C_0402_1005Metric","","Unpolarized capacitor","21",""
"C38","1","0.1uF","","","","","${EXCLUDE_FROM_POS_FILES}","Capacitor_SMD:C_0805_2012Metric","","Unpolarized capacitor","22",""
"C40","1","22uF, 6.3V","","","","","${EXCLUDE_FROM_POS_FILES}","Capacitor_SMD:C_0805_2012Metric","","Unpolarized capacitor","23",""
"C41,C49","2","0.1uF, 25V","","","","","${EXCLUDE_FROM_POS_FILES}","Capacitor_SMD:C_0402_1005Metric","","Unpolarized capacitor","24",""
"C42,C43,C82,C86,C103,C112,C477,C478,C495,C496","10","100pF","","","","","${EXCLUDE_FROM_POS_FILES}","Capacitor_SMD:C_0402_1005Metric","","Unpolarized capacitor","25",""
"C44","1","10nF, 10V","","","","","${EXCLUDE_FROM_POS_FILES}","Capacitor_SMD:C_0402_1005Metric","","Unpolarized capacitor","26",""
"C46,C79,C83,C109","4","10nF","","","","","${EXCLUDE_FROM_POS_FILES}","Capacitor_SMD:C_0402_1005Metric","","Unpolarized capacitor","27",""
"C47","1","3.3nF","","","","","${EXCLUDE_FROM_POS_FILES}","Capacitor_SMD:C_0402_1005Metric","","Unpolarized capacitor","28",""
"C51","1","2.2nF","","","","","${EXCLUDE_FROM_POS_FILES}","Capacitor_SMD:C_0402_1005Metric","","Unpolarized capacitor","29",""
"C53,C54,C55,C56","4","47uF,4V","","","","","${EXCLUDE_FROM_POS_FILES}","Capacitor_SMD:C_1206_3216Metric","","Unpolarized capacitor","30",""
"C57,C97,C99,C107,C113","5","47uF","","","","","${EXCLUDE_FROM_POS_FILES}","Capacitor_SMD:C_1206_3216Metric","","Unpolarized capacitor","31",""
"C76,C78,C104","3","0.1uF 25v","","","","","${EXCLUDE_FROM_POS_FILES}","Capacitor_SMD:C_0402_1005Metric","","Unpolarized capacitor","32",""
"C77,C121,C122,C123,C124,C125,C126,C127,C128,C129,C130,C131,C132,C133,C134,C135,C136,C137,C138,C139,C140,C141,C142,C143,C144,C145,C146,C147,C148,C149,C150,C151,C152,C153,C155,C156,C157,C158,C159,C160,C161,C162,C163,C164,C165,C166,C167,C168,C169,C170,C171,C172,C173,C175,C176,C177,C178,C179,C180,C181,C182,C183,C184,C185,C186,C187,C188,C189,C190,C191,C192,C193,C194,C195,C196,C197,C198,C199,C200,C201,C202,C203,C204,C205,C206,C207,C208,C209,C210,C211,C212,C213,C214,C215,C216,C217,C218,C219,C220,C221,C222,C223,C224,C225,C226,C227,C228,C229,C230,C231,C232,C233,C234,C235,C236,C237,C238,C239,C240,C241,C242,C243,C244,C245,C246,C247,C248,C249,C250,C251,C252,C253,C254,C255,C256,C257,C258,C259,C260,C261,C262,C263,C264,C265,C266,C267,C268,C269,C270,C271,C272,C273,C274,C275,C276,C277,C278,C279,C280,C281,C282,C283,C284,C285,C286,C287,C288,C289,C290,C291,C292,C293,C294,C295,C296,C297,C298,C299,C300,C301,C302,C303,C304,C305,C306,C307,C308,C309,C310,C311,C312,C313,C314,C315,C316,C317,C318,C319,C320,C321,C322,C323,C324,C325,C326,C327,C328,C329,C330,C331,C332,C333,C334,C335,C336,C337,C338,C339,C340,C341,C343,C345,C347,C349,C351,C354,C356,C358,C360,C362,C363,C364,C365,C366,C367,C371,C374,C376,C377,C378,C379,C384,C386,C387,C388,C389,C390,C397,C399,C401,C402,C403,C405,C406,C407,C410,C411,C432,C433,C434,C435,C436,C437,C438,C439,C440,C441,C442,C443,C444,C445,C446,C447,C483,C485,C487,C489,C493,C494,C501,C502,C503,C504,C505,C506,C508,C509,C510,C511,C512,C513,C514,C515,C516,C517,C519,C520,C521,C522,C523","300","0.1uF","","","","","${EXCLUDE_FROM_POS_FILES}","Capacitor_SMD:C_0402_1005Metric","","Unpolarized capacitor","33",""
"C80,C84,C91,C96,C110,C118","6","22uf 25v","","","","","${EXCLUDE_FROM_POS_FILES}","Capacitor_SMD:C_0805_2012Metric","","Unpolarized capacitor","34",""
"C87,C88,C114,C481,C482","5","22pF","","","","","${EXCLUDE_FROM_POS_FILES}","Capacitor_SMD:C_0402_1005Metric","","Unpolarized capacitor","35",""
"C89,C90,C92,C93,C115,C116","6","47uF 6.3V","","","","","${EXCLUDE_FROM_POS_FILES}","Capacitor_SMD:C_1206_3216Metric","","Unpolarized capacitor","36",""
"C154,C174","2","47uF","","","","","${EXCLUDE_FROM_POS_FILES}","Capacitor_SMD:C_1210_3225Metric","","Unpolarized capacitor","37",""
"C368,C369,C370,C380,C381,C382,C383,C392,C422","9","1nF","","","","","${EXCLUDE_FROM_POS_FILES}","Capacitor_SMD:C_0402_1005Metric","","Unpolarized capacitor","38",""
"C372,C373,C408,C409","4","33pF","","","","","${EXCLUDE_FROM_POS_FILES}","Capacitor_SMD:C_0402_1005Metric","","Unpolarized capacitor","39",""
"C375,C385","2","22uF","","","","","${EXCLUDE_FROM_POS_FILES}","Capacitor_SMD:C_0402_1005Metric","","Unpolarized capacitor","40",""
"C424,C429,C431","3","10uF","","","","","${EXCLUDE_FROM_POS_FILES}","Capacitor_SMD:C_0805_2012Metric","","Unpolarized capacitor","41",""
"C473","1","0.56 nF","","","","","${EXCLUDE_FROM_POS_FILES}","Capacitor_SMD:C_0402_1005Metric","","Unpolarized capacitor","42",""
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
